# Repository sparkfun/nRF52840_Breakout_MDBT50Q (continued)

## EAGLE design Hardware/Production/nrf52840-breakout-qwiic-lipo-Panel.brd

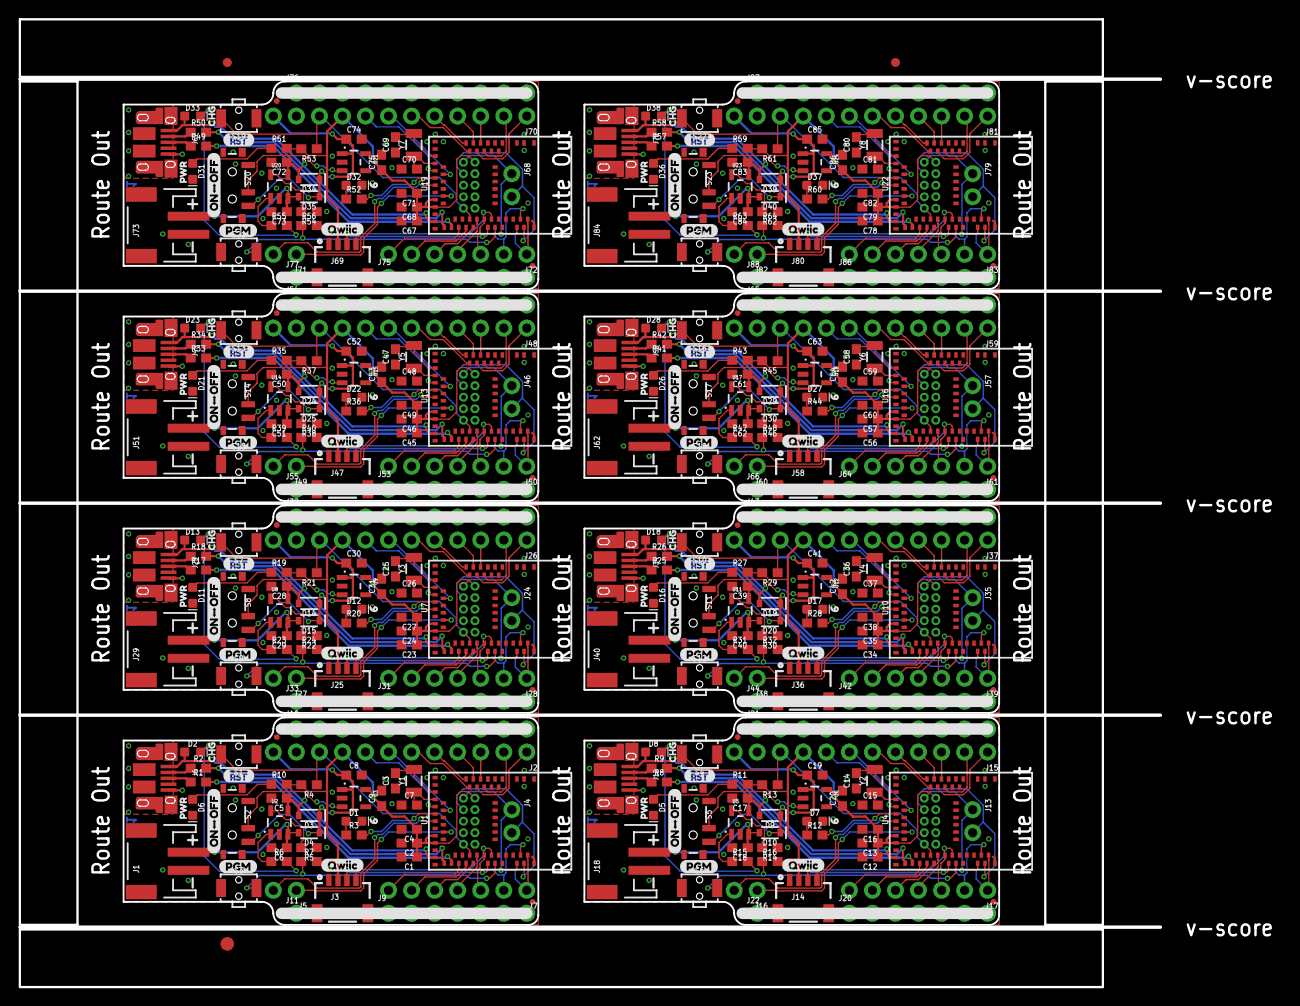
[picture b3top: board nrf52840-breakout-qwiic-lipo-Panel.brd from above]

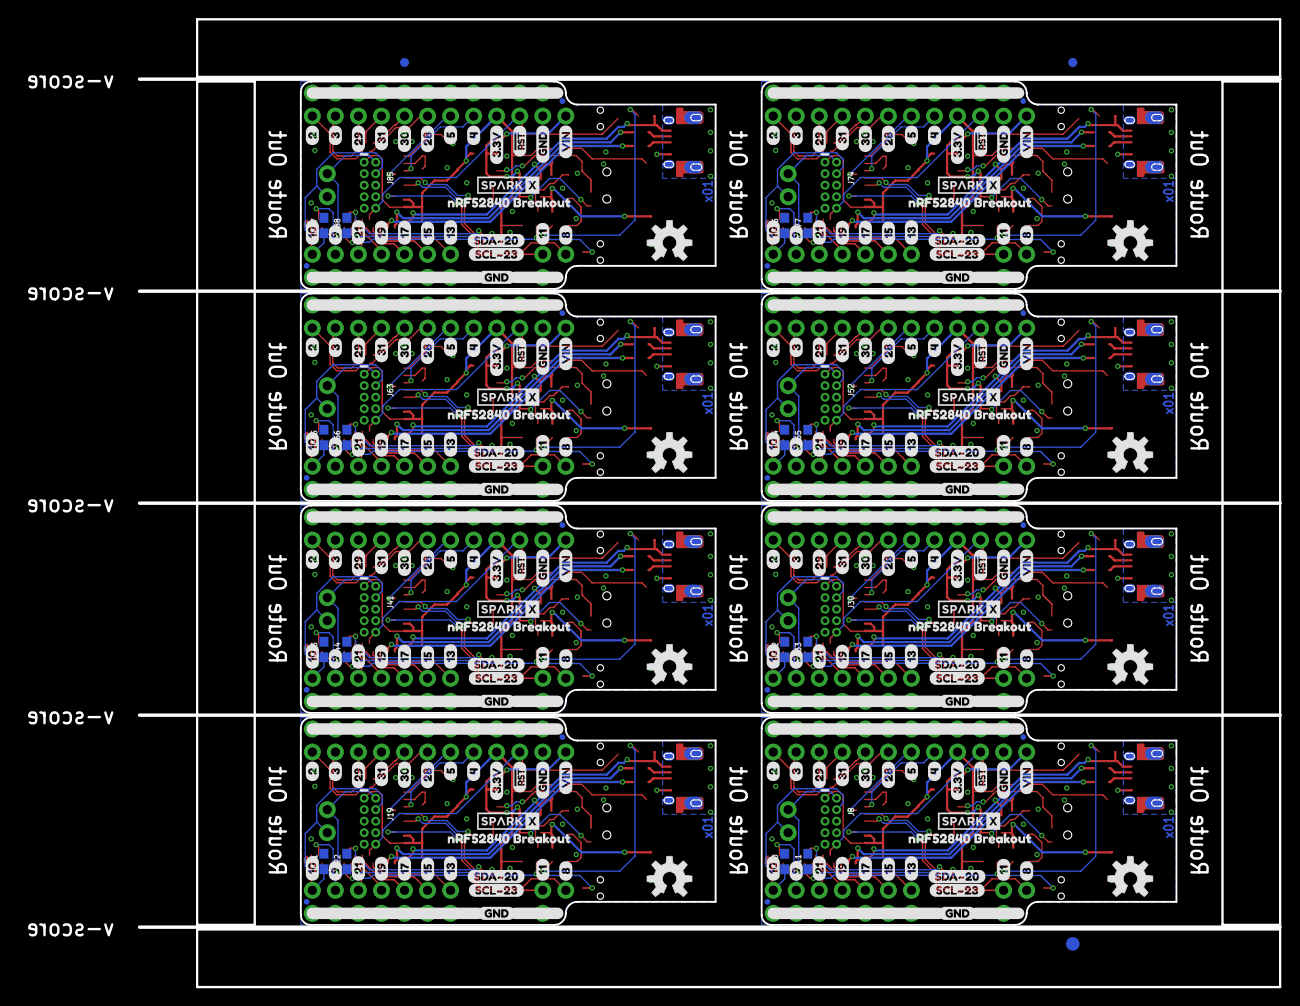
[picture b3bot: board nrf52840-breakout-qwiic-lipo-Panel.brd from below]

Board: 2 copper layers, 125.7 x 106.7 mm, 646 parts (259 on the bottom side), 336 nets.

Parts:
C1, C4, C12, C16, C23, C27, C34, C38, C45, C49, C56, C60, C67, C71, C78, C82: 10uF; 0603
C2, C13, C24, C35, C46, C57, C68, C79: 0.1uF; 0603
C3, C7, C14, C15, C25, C26, C36, C37, C47, C48, C58, C59, C69, C70, C80, C81: 15pF; 0603
C5, C6, C17, C18, C28, C29, C39, C40, C50, C51, C61, C62, C72, C73, C83, C84: 4.7uF; 0603
C8, C9, C19, C20, C30, C31, C41, C42, C52, C53, C63, C64, C74, C75, C85, C86: 1.0uF; 0603
C10, C11, C21, C22, C32, C33, C43, C44, C54, C55, C65, C66, C76, C77, C87, C88: DNP; 0603
D1, D7, D12, D17, D22, D27, D32, D37: GREEN; LED-0603
D2, D8, D13, D18, D23, D28, D33, D38: Yellow; LED-0603
D3, D4, D9, D10, D14, D15, D19, D20, D24, D25, D29, D30, D34, D35, D39, D40: 1A/23V/620mV; SOD-323
D5, D6, D11, D16, D21, D26, D31, D36: RED; LED-0603
E$1, E$2, E$3, E$4: FIDUCIAL-1X2
E$5, E$6: FIDUCIAL-1.5X3
FD1, FD2, FD3, FD4, FD5, FD6, FD7, FD8, FD9, FD10, FD11, FD12, FD13, FD14, FD15, FD16, FD17, FD18, FD19, FD20, FD21, FD22, FD23, FD24, FD25, FD26, FD27, FD28, FD29, FD30, FD31, FD32: FIDUCIALUFIDUCIAL; FIDUCIAL-MICRO
J1, J18, J29, J40, J51, J62, J73, J84: JST-2-SMD
J2, J15, J26, J37, J48, J59, J70, J81: 1X12_NO_SILK
J3, J14, J25, J36, J47, J58, J69, J80: 1X04_1MM_RA
J4, J5, J13, J16, J24, J27, J35, J38, J46, J49, J57, J60, J68, J71, J79, J82: 1X02_NO_SILK
J6, J12, J23, J34, J45, J56, J67, J78: USB-MICROB-PTH-MILL
J7, J9, J17, J20, J28, J31, J39, J42, J50, J53, J61, J64, J72, J75, J83, J86: 1X07_NO_SILK
J8, J19, J30, J41, J52, J63, J74, J85: CORTEX_DEBUG_PTH; 2X5-PTH-1.27MM
J10, J21, J32, J43, J54, J65, J76, J87: 1X11_NO_SILK
J11, J22, J33, J44, J55, J66, J77, J88: 1X01_NO_SILK
LOGO1, LOGO3, LOGO5, LOGO7, LOGO9, LOGO11, LOGO13, LOGO15: SPARKX-LOGO3; SPARKX-SMALL
LOGO2, LOGO4, LOGO6, LOGO8, LOGO10, LOGO12, LOGO14, LOGO16: OSHW-LOGOM; OSHW-LOGO-M
R1, R2, R8, R9, R17, R18, R25, R26, R33, R34, R41, R42, R49, R50, R57, R58: 27; 0603
R3, R6, R10, R11, R12, R15, R19, R20, R23, R27, R28, R31, R35, R36, R39, R43, R44, R47, R51, R52, R55, R59, R60, R63: 1k; 0603
R4, R7, R13, R16, R21, R24, R29, R32, R37, R40, R45, R48, R53, R56, R61, R64: 10k; 0603
R5, R14, R22, R30, R38, R46, R54, R62: 2.0k; 0603
S1, S4, S7, S10, S13, S16, S19, S22: RESET; TACTILE_SWITCH_SMD_RIGHT_ANGLE
S2, S5, S8, S11, S14, S17, S20, S23: SWITCH_SPST_SMD_A
S3, S6, S9, S12, S15, S18, S21, S24: BOOTLOAD; TACTILE_SWITCH_SMD_RIGHT_ANGLE
U1, U4, U7, U10, U13, U16, U19, U22: MDBT50Q
U2, U5, U8, U11, U14, U17, U20, U23: MCP73831; SOT23-5
U3, U6, U9, U12, U15, U18, U21, U24: 3.3V; SOT23-5
U$1, U$63, U$95, U$127, U$159, U$191, U$223, U$255: 625
U$2, U$28, U$65, U$97, U$129, U$161, U$193, U$225: #RST7
U$3, U$34, U$66, U$98, U$130, U$162, U$194, U$226: PGM2
U$4, U$35, U$67, U$99, U$131, U$163, U$195, U$227: ON#OFF4
U$5, U$36, U$68, U$100, U$132, U$164, U$196, U$228: CHG26
U$6, U$37, U$69, U$101, U$133, U$165, U$197, U$229: PWR27
U$7, U$64, U$96, U$128, U$160, U$192, U$224, U$256: 1125
U$8, U$38, U$70, U$102, U$134, U$166, U$198, U$230: QWIIC0
U$9, U$40, U$72, U$104, U$136, U$168, U$200, U$232: 20
U$10, U$41, U$73, U$105, U$137, U$169, U$201, U$233: 31
U$11, U$42, U$74, U$106, U$138, U$170, U$202, U$234: 292
U$12, U$43, U$75, U$107, U$139, U$171, U$203, U$235: 313
U$13, U$44, U$76, U$108, U$140, U$172, U$204, U$236: 304
U$14, U$45, U$77, U$109, U$141, U$173, U$205, U$237: 285
U$15, U$46, U$78, U$110, U$142, U$174, U$206, U$238: 521
U$16, U$47, U$79, U$111, U$143, U$175, U$207, U$239: 421
U$17, U$48, U$80, U$112, U$144, U$176, U$208, U$240: 3#3V5
U$18, U$49, U$81, U$113, U$145, U$177, U$209, U$241: #RST6
U$19, U$50, U$82, U$114, U$146, U$178, U$210, U$242: GND7
U$20, U$51, U$83, U$115, U$147, U$179, U$211, U$243: VIN8
U$21, U$52, U$84, U$116, U$148, U$180, U$212, U$244: 1022
U$22, U$53, U$85, U$117, U$149, U$181, U$213, U$245: 916
U$23, U$54, U$86, U$118, U$150, U$182, U$214, U$246: 2111
U$24, U$55, U$87, U$119, U$151, U$183, U$215, U$247: 1912
U$25, U$56, U$88, U$120, U$152, U$184, U$216, U$248: 1713
U$26, U$57, U$89, U$121, U$153, U$185, U$217, U$249: 1522
U$27, U$58, U$90, U$122, U$154, U$186, U$218, U$250: 1314
U$29, U$59, U$91, U$123, U$155, U$187, U$219, U$251: 816
U$30, U$39, U$71, U$103, U$135, U$167, U$199, U$231: GND6
U$31, U$60, U$92, U$124, U$156, U$188, U$220, U$252: NRF52840_BREAKOUT17
U$32, U$61, U$93, U$125, U$157, U$189, U$221, U$253: SCL#2323
U$33, U$62, U$94, U$126, U$158, U$190, U$222, U$254: SDA#2024
Y1, Y2, Y3, Y4, Y5, Y6, Y7, Y8: 32.768kHz; CRYSTAL-SMD-3.2X1.5MM

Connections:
3.3V: C1.1, C2.1, C4.1, C9.1, J2.9, J3.2, J8.1, R4.2, R7.2, R10.2, U1.28, U1.30, U3.5
3.3V1: C12.1, C13.1, C16.1, C20.1, J14.2, J15.9, J19.1, R11.2, R13.2, R16.2, U4.28, U4.30, U6.5
3.3V2: C23.1, C24.1, C27.1, C31.1, J25.2, J26.9, J30.1, R19.2, R21.2, R24.2, U7.28, U7.30, U9.5
3.3V3: C34.1, C35.1, C38.1, C42.1, J36.2, J37.9, J41.1, R27.2, R29.2, R32.2, U10.28, U10.30, U12.5
3.3V4: C45.1, C46.1, C49.1, C53.1, J47.2, J48.9, J52.1, R35.2, R37.2, R40.2, U13.28, U13.30, U15.5
3.3V5: C56.1, C57.1, C60.1, C64.1, J58.2, J59.9, J63.1, R43.2, R45.2, R48.2, U16.28, U16.30, U18.5
3.3V6: C67.1, C68.1, C71.1, C75.1, J69.2, J70.9, J74.1, R51.2, R53.2, R56.2, U19.28, U19.30, U21.5
3.3V7: C78.1, C79.1, C82.1, C86.1, J80.2, J81.9, J85.1, R59.2, R61.2, R64.2, U22.28, U22.30, U24.5
!RESET: J2.10, J8.10, R4.1, S1.2, U1.40
!RESET1: J15.10, J19.10, R13.1, S4.2, U4.40
!RESET2: J26.10, J30.10, R21.1, S7.2, U7.40
!RESET3: J37.10, J41.10, R29.1, S10.2, U10.40
!RESET4: J48.10, J52.10, R37.1, S13.2, U13.40
!RESET5: J59.10, J63.10, R45.1, S16.2, U16.40
!RESET6: J70.10, J74.10, R53.1, S19.2, U19.40
!RESET7: J81.10, J85.10, R61.1, S22.2, U22.40
D+: R1.2, U1.35
D+1: R8.2, U4.35
D+2: R17.2, U7.35
D+3: R25.2, U10.35
D+4: R33.2, U13.35
D+5: R41.2, U16.35
D+6: R49.2, U19.35
D+7: R57.2, U22.35
D+_CON: J6.D+, R1.1
D+_CON1: J12.D+, R8.1
D+_CON2: J23.D+, R17.1
D+_CON3: J34.D+, R25.1
D+_CON4: J45.D+, R33.1
D+_CON5: J56.D+, R41.1
D+_CON6: J67.D+, R49.1
D+_CON7: J78.D+, R57.1
D-: R2.2, U1.34
D-1: R9.2, U4.34
D-2: R18.2, U7.34
D-3: R26.2, U10.34
D-4: R34.2, U13.34
D-5: R42.2, U16.34
D-6: R50.2, U19.34
D-7: R58.2, U22.34
D-_CON: J6.D-, R2.1
D-_CON1: J12.D-, R9.1
D-_CON2: J23.D-, R18.1
D-_CON3: J34.D-, R26.1
D-_CON4: J45.D-, R34.1
D-_CON5: J56.D-, R42.1
D-_CON6: J67.D-, R50.1
D-_CON7: J78.D-, R58.1
GND: C1.2, C2.2, C3.1, C4.2, C5.2, C6.2, C7.1, C8.2, C9.2, C10.2, C11.2, D1.C, D6.C, J1.1, J2.11, J3.1, J6.GND, J8.3, J8.5, J8.9, J9.1, J9.2, J9.3, J9.4, J9.5, J9.6, J9.7, J10.1, J10.2, J10.3, J10.4, J10.5, J10.6, J10.7, J10.8, J10.9, J10.10, J10.11, J11.1, R5.1, S1.1, S2.3, S3.1, U1.1, U1.2, U1.15, U1.33, U1.55, U2.2, U3.2
GND1: C12.2, C13.2, C14.1, C15.1, C16.2, C17.2, C18.2, C19.2, C20.2, C21.2, C22.2, D5.C, D7.C, J12.GND, J14.1, J15.11, J18.1, J19.3, J19.5, J19.9, J20.1, J20.2, J20.3, J20.4, J20.5, J20.6, J20.7, J21.1, J21.2, J21.3, J21.4, J21.5, J21.6, J21.7, J21.8, J21.9, J21.10, J21.11, J22.1, R14.1, S4.1, S5.3, S6.1, U4.1, U4.2, U4.15, U4.33, U4.55, U5.2, U6.2
GND2: C23.2, C24.2, C25.1, C26.1, C27.2, C28.2, C29.2, C30.2, C31.2, C32.2, C33.2, D11.C, D12.C, J23.GND, J25.1, J26.11, J29.1, J30.3, J30.5, J30.9, J31.1, J31.2, J31.3, J31.4, J31.5, J31.6, J31.7, J32.1, J32.2, J32.3, J32.4, J32.5, J32.6, J32.7, J32.8, J32.9, J32.10, J32.11, J33.1, R22.1, S7.1, S8.3, S9.1, U7.1, U7.2, U7.15, U7.33, U7.55, U8.2, U9.2
GND3: C34.2, C35.2, C36.1, C37.1, C38.2, C39.2, C40.2, C41.2, C42.2, C43.2, C44.2, D16.C, D17.C, J34.GND, J36.1, J37.11, J40.1, J41.3, J41.5, J41.9, J42.1, J42.2, J42.3, J42.4, J42.5, J42.6, J42.7, J43.1, J43.2, J43.3, J43.4, J43.5, J43.6, J43.7, J43.8, J43.9, J43.10, J43.11, J44.1, R30.1, S10.1, S11.3, S12.1, U10.1, U10.2, U10.15, U10.33, U10.55, U11.2, U12.2
GND4: C45.2, C46.2, C47.1, C48.1, C49.2, C50.2, C51.2, C52.2, C53.2, C54.2, C55.2, D21.C, D22.C, J45.GND, J47.1, J48.11, J51.1, J52.3, J52.5, J52.9, J53.1, J53.2, J53.3, J53.4, J53.5, J53.6, J53.7, J54.1, J54.2, J54.3, J54.4, J54.5, J54.6, J54.7, J54.8, J54.9, J54.10, J54.11, J55.1, R38.1, S13.1, S14.3, S15.1, U13.1, U13.2, U13.15, U13.33, U13.55, U14.2, U15.2
GND5: C56.2, C57.2, C58.1, C59.1, C60.2, C61.2, C62.2, C63.2, C64.2, C65.2, C66.2, D26.C, D27.C, J56.GND, J58.1, J59.11, J62.1, J63.3, J63.5, J63.9, J64.1, J64.2, J64.3, J64.4, J64.5, J64.6, J64.7, J65.1, J65.2, J65.3, J65.4, J65.5, J65.6, J65.7, J65.8, J65.9, J65.10, J65.11, J66.1, R46.1, S16.1, S17.3, S18.1, U16.1, U16.2, U16.15, U16.33, U16.55, U17.2, U18.2
GND6: C67.2, C68.2, C69.1, C70.1, C71.2, C72.2, C73.2, C74.2, C75.2, C76.2, C77.2, D31.C, D32.C, J67.GND, J69.1, J70.11, J73.1, J74.3, J74.5, J74.9, J75.1, J75.2, J75.3, J75.4, J75.5, J75.6, J75.7, J76.1, J76.2, J76.3, J76.4, J76.5, J76.6, J76.7, J76.8, J76.9, J76.10, J76.11, J77.1, R54.1, S19.1, S20.3, S21.1, U19.1, U19.2, U19.15, U19.33, U19.55, U20.2, U21.2
GND7: C78.2, C79.2, C80.1, C81.1, C82.2, C83.2, C84.2, C85.2, C86.2, C87.2, C88.2, D36.C, D37.C, J78.GND, J80.1, J81.11, J84.1, J85.3, J85.5, J85.9, J86.1, J86.2, J86.3, J86.4, J86.5, J86.6, J86.7, J87.1, J87.2, J87.3, J87.4, J87.5, J87.6, J87.7, J87.8, J87.9, J87.10, J87.11, J88.1, R62.1, S22.1, S23.3, S24.1, U22.1, U22.2, U22.15, U22.33, U22.55, U23.2, U24.2
unnamed: R5.2, U2.5
unnamed: S2.2, U3.3
unnamed: D2.C, R6.2
unnamed: R6.1, U2.1
unnamed: D5.A, R11.1
unnamed: D7.A, R12.1
unnamed: D1.A, R3.1
unnamed: R14.2, U5.5
unnamed: D8.C, R15.2
unnamed: D6.A, R10.1
unnamed: R15.1, U5.1
unnamed: S5.2, U6.3
unnamed: D11.A, R19.1
unnamed: D12.A, R20.1
unnamed: R22.2, U8.5
unnamed: D13.C, R23.2
unnamed: R23.1, U8.1
unnamed: S8.2, U9.3
unnamed: D16.A, R27.1
unnamed: D17.A, R28.1
unnamed: R30.2, U11.5
unnamed: D18.C, R31.2
unnamed: R31.1, U11.1
unnamed: S11.2, U12.3
unnamed: D21.A, R35.1
unnamed: D22.A, R36.1
unnamed: R38.2, U14.5
unnamed: D23.C, R39.2
unnamed: R39.1, U14.1
unnamed: S14.2, U15.3
unnamed: D26.A, R43.1
unnamed: D27.A, R44.1
unnamed: R46.2, U17.5
unnamed: D28.C, R47.2
unnamed: R47.1, U17.1
unnamed: S17.2, U18.3
unnamed: D31.A, R51.1
unnamed: D32.A, R52.1
unnamed: R54.2, U20.5
unnamed: D33.C, R55.2
unnamed: R55.1, U20.1
unnamed: S20.2, U21.3
unnamed: D36.A, R59.1
unnamed: D37.A, R60.1
unnamed: R62.2, U23.5
unnamed: D38.C, R63.2
unnamed: R63.1, U23.1
unnamed: S23.2, U24.3
P0.01: J17.7, U4.37
P0.02: J17.6, U4.39
P0.02/AIN0: J2.1, U1.11
P0.02/AIN1: J15.1, U4.11
P0.02/AIN2: J26.1, U7.11
P0.02/AIN3: J37.1, U10.11
P0.02/AIN4: J48.1, U13.11
P0.02/AIN5: J59.1, U16.11
P0.02/AIN6: J70.1, U19.11
P0.02/AIN7: J81.1, U22.11
P0.03: J17.5, U4.41
P0.03/AIN1: J2.2, U1.9
P0.03/AIN2: J15.2, U4.9
P0.03/AIN3: J26.2, U7.9
P0.03/AIN4: J37.2, U10.9
P0.03/AIN5: J48.2, U13.9
P0.03/AIN6: J59.2, U16.9
P0.03/AIN7: J70.2, U19.9
P0.03/AIN8: J81.2, U22.9
P0.04: J17.4, U4.42
P0.04/AIN1: J15.8, U4.20
P0.04/AIN2: J2.8, U1.20
P0.04/AIN3: J26.8, U7.20
P0.04/AIN4: J37.8, U10.20
P0.04/AIN5: J48.8, U13.20
P0.04/AIN6: J59.8, U16.20
P0.04/AIN7: J70.8, U19.20
P0.04/AIN8: J81.8, U22.20
P0.05: J14.3, U4.44
P0.05/AIN1: J15.7, U4.21
P0.05/AIN2: J26.7, U7.21
P0.05/AIN3: J2.7, U1.21
P0.05/AIN4: J37.7, U10.21
P0.05/AIN5: J48.7, U13.21
P0.05/AIN6: J59.7, U16.21
P0.05/AIN7: J70.7, U19.21
P0.05/AIN8: J81.7, U22.21
P0.06: R3.2, U1.22
P0.07: J17.3, U4.43
P0.08: J5.2, U1.24
P0.09: R16.1, S6.2, U4.46
P0.09/NFC1: C11.1, J7.2, U1.52
P0.09/NFC2: C22.1, J17.2, U4.52
P0.09/NFC3: C33.1, J28.2, U7.52
P0.09/NFC4: C44.1, J39.2, U10.52
P0.09/NFC5: C55.1, J50.2, U13.52
P0.09/NFC6: C66.1, J61.2, U16.52
P0.09/NFC7: C77.1, J72.2, U19.52
P0.09/NFC8: C88.1, J83.2, U22.52
P0.10: J14.4, U4.45
P0.10/NFC1: C21.1, J17.1, U4.54
P0.10/NFC2: C10.1, J7.1, U1.54
P0.10/NFC3: C32.1, J28.1, U7.54
P0.10/NFC4: C43.1, J39.1, U10.54
P0.10/NFC5: C54.1, J50.1, U13.54
P0.10/NFC6: C65.1, J61.1, U16.54
P0.10/NFC7: C76.1, J72.1, U19.54
P0.10/NFC8: C87.1, J83.1, U22.54
P0.11: J5.1, U1.27
P0.12: R12.2, U4.22
P0.13: J7.7, U1.37
P0.14: J16.2, U4.24
P0.15: J7.6, U1.39
P0.16: J16.1, U4.27
P0.17: J7.5, U1.41
P0.18: J28.7, U7.37
P0.19: J7.4, U1.42
P0.20: J3.3, U1.44
P0.21: J7.3, U1.43
P0.22: R7.1, S3.2, U1.46
P0.23: J3.4, U1.45
P0.24: J28.6, U7.39
P0.25: J28.5, U7.41
P0.26: J28.4, U7.42
P0.27: J25.3, U7.44
P0.28: J28.3, U7.43
P0.28/AIN1: J15.6, U4.13
P0.28/AIN2: J26.6, U7.13
P0.28/AIN3: J37.6, U10.13
P0.28/AIN4: J2.6, U1.13
P0.28/AIN5: J48.6, U13.13
P0.28/AIN6: J59.6, U16.13
P0.28/AIN7: J70.6, U19.13
P0.28/AIN8: J81.6, U22.13
P0.29: R24.1, S9.2, U7.46
P0.29/AIN1: J15.3, U4.10
P0.29/AIN2: J26.3, U7.10
P0.29/AIN3: J37.3, U10.10
P0.29/AIN4: J48.3, U13.10
P0.29/AIN5: J2.3, U1.10
P0.29/AIN6: J59.3, U16.10
P0.29/AIN7: J70.3, U19.10
P0.29/AIN8: J81.3, U22.10
P0.30: J25.4, U7.45
P0.30/AIN1: J15.5, U4.14
P0.30/AIN2: J26.5, U7.14
P0.30/AIN3: J37.5, U10.14
P0.30/AIN4: J48.5, U13.14
P0.30/AIN5: J59.5, U16.14
P0.30/AIN6: J2.5, U1.14
P0.30/AIN7: J70.5, U19.14
P0.30/AIN8: J81.5, U22.14
P0.31: R20.2, U7.22
P0.31/AIN1: J15.4, U4.12
P0.31/AIN2: J26.4, U7.12
P0.31/AIN3: J37.4, U10.12
P0.31/AIN4: J48.4, U13.12
P0.31/AIN5: J59.4, U16.12
P0.31/AIN6: J70.4, U19.12
P0.31/AIN7: J2.4, U1.12
P0.31/AIN8: J81.4, U22.12
P0.32: J27.2, U7.24
P0.33: J27.1, U7.27
P0.34: J39.7, U10.37
P0.35: J39.6, U10.39
P0.36: J39.5, U10.41
P0.37: J39.4, U10.42
P0.38: J36.3, U10.44
P0.39: J39.3, U10.43
P0.40: R32.1, S12.2, U10.46
P0.41: J36.4, U10.45
P0.42: R28.2, U10.22
P0.43: J38.2, U10.24
P0.44: J38.1, U10.27
P0.45: J50.7, U13.37
P0.46: J50.6, U13.39
P0.47: J50.5, U13.41
P0.48: J50.4, U13.42
P0.49: J47.3, U13.44
P0.50: J50.3, U13.43
P0.51: R40.1, S15.2, U13.46
P0.52: J47.4, U13.45
P0.53: R36.2, U13.22
P0.54: J49.2, U13.24
P0.55: J49.1, U13.27
P0.56: J61.7, U16.37
P0.57: J61.6, U16.39
P0.58: J61.5, U16.41
P0.59: J61.4, U16.42
P0.60: J58.3, U16.44
P0.61: J61.3, U16.43
P0.62: R48.1, S18.2, U16.46
P0.63: J58.4, U16.45
P0.64: R44.2, U16.22
P0.65: J60.2, U16.24
P0.66: J60.1, U16.27
P0.67: J72.7, U19.37
P0.68: J72.6, U19.39
P0.69: J72.5, U19.41
P0.70: J72.4, U19.42
P0.71: J69.3, U19.44
P0.72: J72.3, U19.43
P0.73: R56.1, S21.2, U19.46
P0.74: J69.4, U19.45
P0.75: R52.2, U19.22
P0.76: J71.2, U19.24
P0.77: J71.1, U19.27
P0.78: J83.7, U22.37
P0.79: J83.6, U22.39
P0.80: J83.5, U22.41
P0.81: J83.4, U22.42
P0.82: J80.3, U22.44
P0.83: J83.3, U22.43
P0.84: R64.1, S24.2, U22.46
P0.85: J80.4, U22.45
P0.86: R60.2, U22.22
P0.87: J82.2, U22.24
P0.88: J82.1, U22.27
SHIELD: J6.SHIELD, J6.SHIELD2, J6.SHIELD3, J6.SHIELD4, J6.SHIELD5, J6.SHIELD6, J6.SHIELD7, J6.SHIELD8, J6.SHIELD9, J6.SHIELD10
SHIELD1: J12.SHIELD, J12.SHIELD2, J12.SHIELD3, J12.SHIELD4, J12.SHIELD5, J12.SHIELD6, J12.SHIELD7, J12.SHIELD8, J12.SHIELD9, J12.SHIELD10
SHIELD2: J23.SHIELD, J23.SHIELD2, J23.SHIELD3, J23.SHIELD4, J23.SHIELD5, J23.SHIELD6, J23.SHIELD7, J23.SHIELD8, J23.SHIELD9, J23.SHIELD10
SHIELD3: J34.SHIELD, J34.SHIELD2, J34.SHIELD3, J34.SHIELD4, J34.SHIELD5, J34.SHIELD6, J34.SHIELD7, J34.SHIELD8, J34.SHIELD9, J34.SHIELD10
SHIELD4: J45.SHIELD, J45.SHIELD2, J45.SHIELD3, J45.SHIELD4, J45.SHIELD5, J45.SHIELD6, J45.SHIELD7, J45.SHIELD8, J45.SHIELD9, J45.SHIELD10
SHIELD5: J56.SHIELD, J56.SHIELD2, J56.SHIELD3, J56.SHIELD4, J56.SHIELD5, J56.SHIELD6, J56.SHIELD7, J56.SHIELD8, J56.SHIELD9, J56.SHIELD10
SHIELD6: J67.SHIELD, J67.SHIELD2, J67.SHIELD3, J67.SHIELD4, J67.SHIELD5, J67.SHIELD6, J67.SHIELD7, J67.SHIELD8, J67.SHIELD9, J67.SHIELD10
SHIELD7: J78.SHIELD, J78.SHIELD2, J78.SHIELD3, J78.SHIELD4, J78.SHIELD5, J78.SHIELD6, J78.SHIELD7, J78.SHIELD8, J78.SHIELD9, J78.SHIELD10
SWDCLK: J4.2, J8.4, U1.53
SWDCLK1: J13.2, J19.4, U4.53
SWDCLK2: J24.2, J30.4, U7.53
SWDCLK3: J35.2, J41.4, U10.53
SWDCLK4: J46.2, J52.4, U13.53
SWDCLK5: J57.2, J63.4, U16.53
SWDCLK6: J68.2, J74.4, U19.53
SWDCLK7: J79.2, J85.4, U22.53
SWDIO: J4.1, J8.2, U1.51
SWDIO1: J13.1, J19.2, U4.51
SWDIO2: J24.1, J30.2, U7.51
SWDIO3: J35.1, J41.2, U10.51
SWDIO4: J46.1, J52.2, U13.51
SWDIO5: J57.1, J63.2, U16.51
SWDIO6: J68.1, J74.2, U19.51
SWDIO7: J79.1, J85.2, U22.51
VIN: C8.1, D3.C, D4.C, J2.12, S2.1, U3.1
VIN1: C19.1, D9.C, D10.C, J15.12, S5.1, U6.1
VIN2: C30.1, D14.C, D15.C, J26.12, S8.1, U9.1
VIN3: C41.1, D19.C, D20.C, J37.12, S11.1, U12.1
VIN4: C52.1, D24.C, D25.C, J48.12, S14.1, U15.1
VIN5: C63.1, D29.C, D30.C, J59.12, S17.1, U18.1
VIN6: C74.1, D34.C, D35.C, J70.12, S20.1, U21.1
VIN7: C85.1, D39.C, D40.C, J81.12, S23.1, U24.1
V_BATT: C6.1, D4.A, J1.2, U2.3
V_BATT1: C18.1, D10.A, J18.2, U5.3
V_BATT2: C29.1, D15.A, J29.2, U8.3
V_BATT3: C40.1, D20.A, J40.2, U11.3
V_BATT4: C51.1, D25.A, J51.2, U14.3
V_BATT5: C62.1, D30.A, J62.2, U17.3
V_BATT6: C73.1, D35.A, J73.2, U20.3
V_BATT7: C84.1, D40.A, J84.2, U23.3
V_USB: C5.1, D2.A, D3.A, J6.VBUS, U1.32, U2.4
V_USB1: C17.1, D8.A, D9.A, J12.VBUS, U4.32, U5.4
V_USB2: C28.1, D13.A, D14.A, J23.VBUS, U7.32, U8.4
V_USB3: C39.1, D18.A, D19.A, J34.VBUS, U10.32, U11.4
V_USB4: C50.1, D23.A, D24.A, J45.VBUS, U13.32, U14.4
V_USB5: C61.1, D28.A, D29.A, J56.VBUS, U16.32, U17.4
V_USB6: C72.1, D33.A, D34.A, J67.VBUS, U19.32, U20.4
V_USB7: C83.1, D38.A, D39.A, J78.VBUS, U22.32, U23.4
XL1: C3.2, U1.17, Y1.P$2
XL2: C7.2, U1.18, Y1.P$1
XL3: C14.2, U4.17, Y2.P$2
XL4: C15.2, U4.18, Y2.P$1
XL5: C25.2, U7.17, Y3.P$2
XL6: C26.2, U7.18, Y3.P$1
XL7: C36.2, U10.17, Y4.P$2
XL8: C37.2, U10.18, Y4.P$1
XL9: C47.2, U13.17, Y5.P$2
XL10: C48.2, U13.18, Y5.P$1
XL11: C58.2, U16.17, Y6.P$2
XL12: C59.2, U16.18, Y6.P$1
XL13: C69.2, U19.17, Y7.P$2
XL14: C70.2, U19.18, Y7.P$1
XL15: C80.2, U22.17, Y8.P$2
XL16: C81.2, U22.18, Y8.P$1

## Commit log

2018-08-30 initial commit -- hardware (x01)
2018-09-18 Adding x01 panel
2018-09-25 Revisions preparing for v10
    - Rearranged pin breakouts, qwiic connection, LED, and button
    - Flipped on/off switch towards module for easier access
    - Expanded board 50mil to facilitate soldering pins near buttons
    - Labeled pins on top side
    - Increased VBAT and VUSB power trace width
2018-09-25 Adding nrf52840 library
2018-09-25 Board revisions post engineer checklist
    - Added extra ground PTH
    - Added production sku for nRF module
    - Added link to tutorial
    - Clean up schematic
2018-09-25 Adding MDBT50Q module datasheet.
2018-09-25 Adding pull-up resistors to I2C lines.
2018-09-27 Engineering review revisions
    - Increase USB data line clearance to 10mil
    - Move silkscreen to better-avoid stop
    - Add silk to indicate ADC pins
    - Minor trace re-routing
2018-09-27 Setting grid to default.
2018-10-03 panel v10 created
2018-10-05 Fixing silk on 28, 29, 30 bottom side
2018-10-05 Flipping board
2018-10-05 Updated silk
2018-11-27 Adding board pin definitions for nRF5 SDK.
2018-11-27 Fixing LED active state definition -- active-high.
2018-11-28 Adding sparkfun board definitions for nRF52 Adafruit.
2018-11-28 Adding notes on Firmware directory
2018-11-28 Adding readme to nRF5 SDK directory.
2018-11-28 Adding BLE button/LED peripheral example.
2018-11-28 Adding optional connect-LED disable.
2019-07-17 Update board definition
    Owen solved compiler issue: Adafruit switch to using TinyUSB in the core. The following changes update the board definition to use TinyUSB
2019-07-17 Update for TinyUSB
    USB is initialized with TinyUSB core in the build.
    https://github.com/sparkfun/nRF52840_Breakout_MDBT50Q/blob/master/Firmware/Arduino/sparkfun_boards.txt#L38
2019-07-20 Update for TinyUSB
    Forgot to remove usb header
2019-07-20 Update License Section
    Add forum support info
2019-09-12 Forum topic removed.
2019-12-18 Update variant.h
    Fixing mismatched analog pin definitions to match schematic and datasheet of the nRF52840 (MDBT50Q).
2020-05-29 Update variant.h
    There are updates to the nRF52 Arduino core files that broke a few things. More information can be found here:
    https://github.com/sparkfun/nRF52840_Breakout_MDBT50Q/issues/7
    Adding additional defines for the hardware uart pins for anyone using nRF52 Arduino Core files, 0.17.0 and above.
2020-06-17 Corrected serial pin definitions
    "Serial" is USB serial, so we don't need to define any hardware pins. Left the original pins for "Serial1" and added the pin definitions for "Serial2".
